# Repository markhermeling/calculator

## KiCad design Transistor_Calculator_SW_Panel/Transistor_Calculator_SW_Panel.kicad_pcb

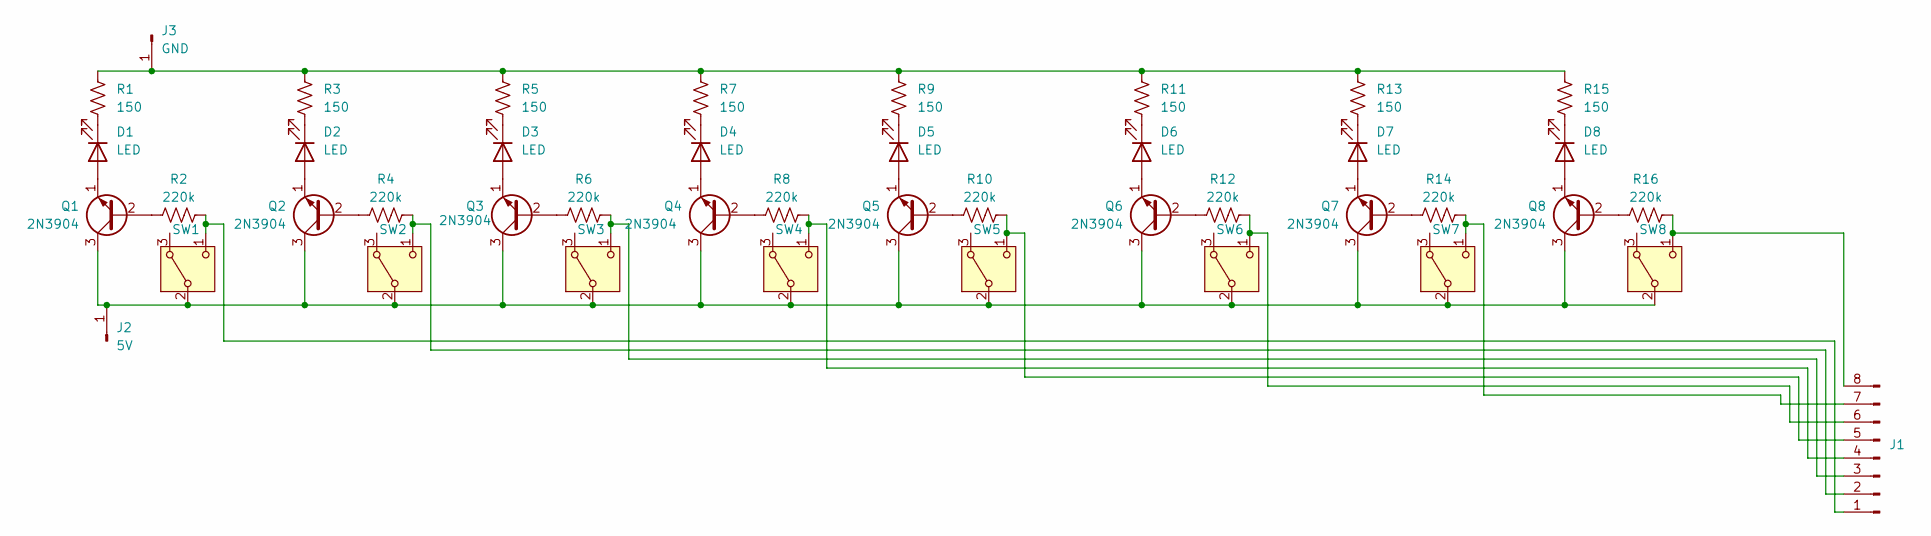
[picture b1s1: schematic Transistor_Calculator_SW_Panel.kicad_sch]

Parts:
D1, D2, D3, D4, D5, D6, D7, D8: LED; LED_D5.0mm_FlatTop
J1: Alex_8-pin
J2: 5V; TestPoint_Pad_D2.0mm
J3: GND; TestPoint_Pad_D2.0mm
Q1, Q2, Q3, Q4, Q5, Q6, Q7, Q8: 2N3904; TO-92L_HandSolder
R1, R3, R5, R7, R9, R11, R13, R15: 150; R_Axial_DIN0204_L3.6mm_D1.6mm_P1.90mm_Vertical
R2, R4, R6, R8, R10, R12, R14, R16: 220k; R_Axial_DIN0204_L3.6mm_D1.6mm_P1.90mm_Vertical
SW1, SW2, SW3, SW4, SW5, SW6, SW7, SW8: Alex_Switch

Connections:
unnamed: D1.2 (A), Q1.1 (E)
unnamed: D1.1 (K), R1.2
unnamed: D2.2 (A), Q2.1 (E)
unnamed: D2.1 (K), R3.2
unnamed: D3.2 (A), Q3.1 (E)
unnamed: D3.1 (K), R5.2
unnamed: D4.2 (A), Q4.1 (E)
unnamed: D4.1 (K), R7.2
unnamed: D5.2 (A), Q5.1 (E)
unnamed: D5.1 (K), R9.2
unnamed: D6.2 (A), Q6.1 (E)
unnamed: D6.1 (K), R11.2
unnamed: D7.2 (A), Q7.1 (E)
unnamed: D7.1 (K), R13.2
unnamed: D8.2 (A), Q8.1 (E)
unnamed: D8.1 (K), R15.2
unnamed: J1.1, R2.2, SW1.1 (C)
unnamed: J1.2, R4.2, SW2.1 (C)
unnamed: J1.3, R6.2, SW3.1 (C)
unnamed: J1.4, R8.2, SW4.1 (C)
unnamed: J1.5, R10.2, SW5.1 (C)
unnamed: J1.6, R12.2, SW6.1 (C)
unnamed: J1.7, R14.2, SW7.1 (C)
unnamed: J1.8, R16.2, SW8.1 (C)
unnamed: J2.1, Q1.3 (C), Q2.3 (C), Q3.3 (C), Q4.3 (C), Q5.3 (C), Q6.3 (C), Q7.3 (C), Q8.3 (C), SW1.2 (B), SW2.2 (B), SW3.2 (B), SW4.2 (B), SW5.2 (B), SW6.2 (B), SW7.2 (B), SW8.2 (B)
unnamed: J3.1, R1.1, R3.1, R5.1, R7.1, R9.1, R11.1, R13.1, R15.1
unnamed: Q1.2 (B), R2.1
unnamed: Q2.2 (B), R4.1
unnamed: Q3.2 (B), R6.1
unnamed: Q4.2 (B), R8.1
unnamed: Q5.2 (B), R10.1
unnamed: Q6.2 (B), R12.1
unnamed: Q7.2 (B), R14.1
unnamed: Q8.2 (B), R16.1

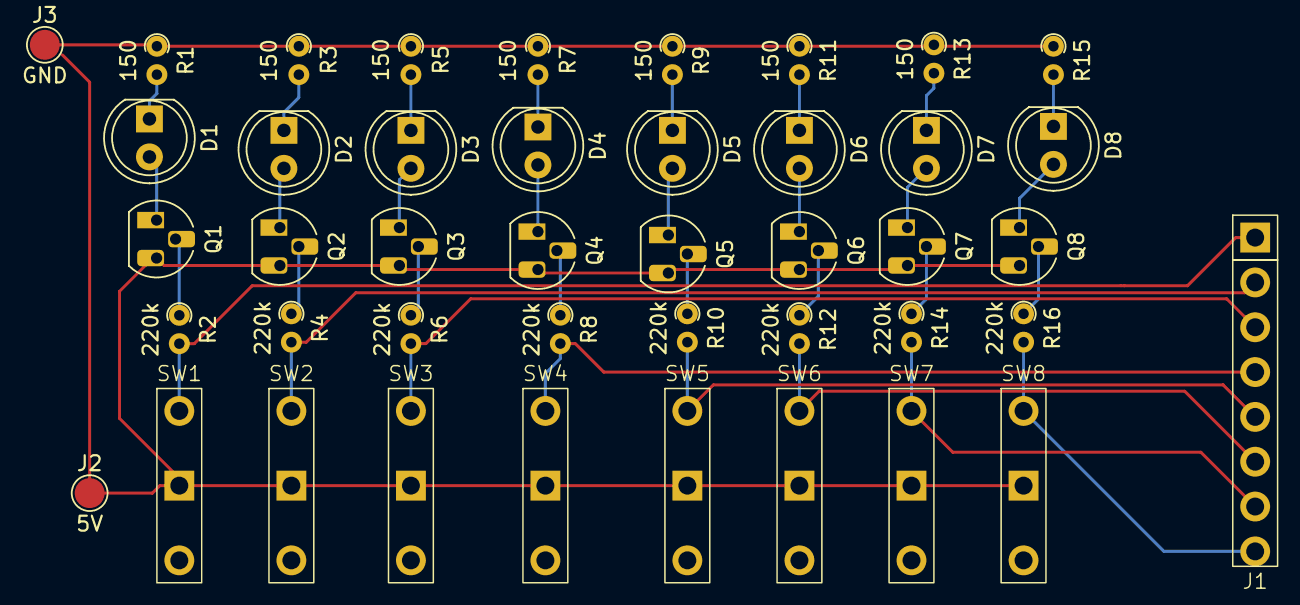
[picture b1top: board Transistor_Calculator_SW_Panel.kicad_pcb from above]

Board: 2 copper layers, 43 parts (0 on the bottom side), 34 nets.

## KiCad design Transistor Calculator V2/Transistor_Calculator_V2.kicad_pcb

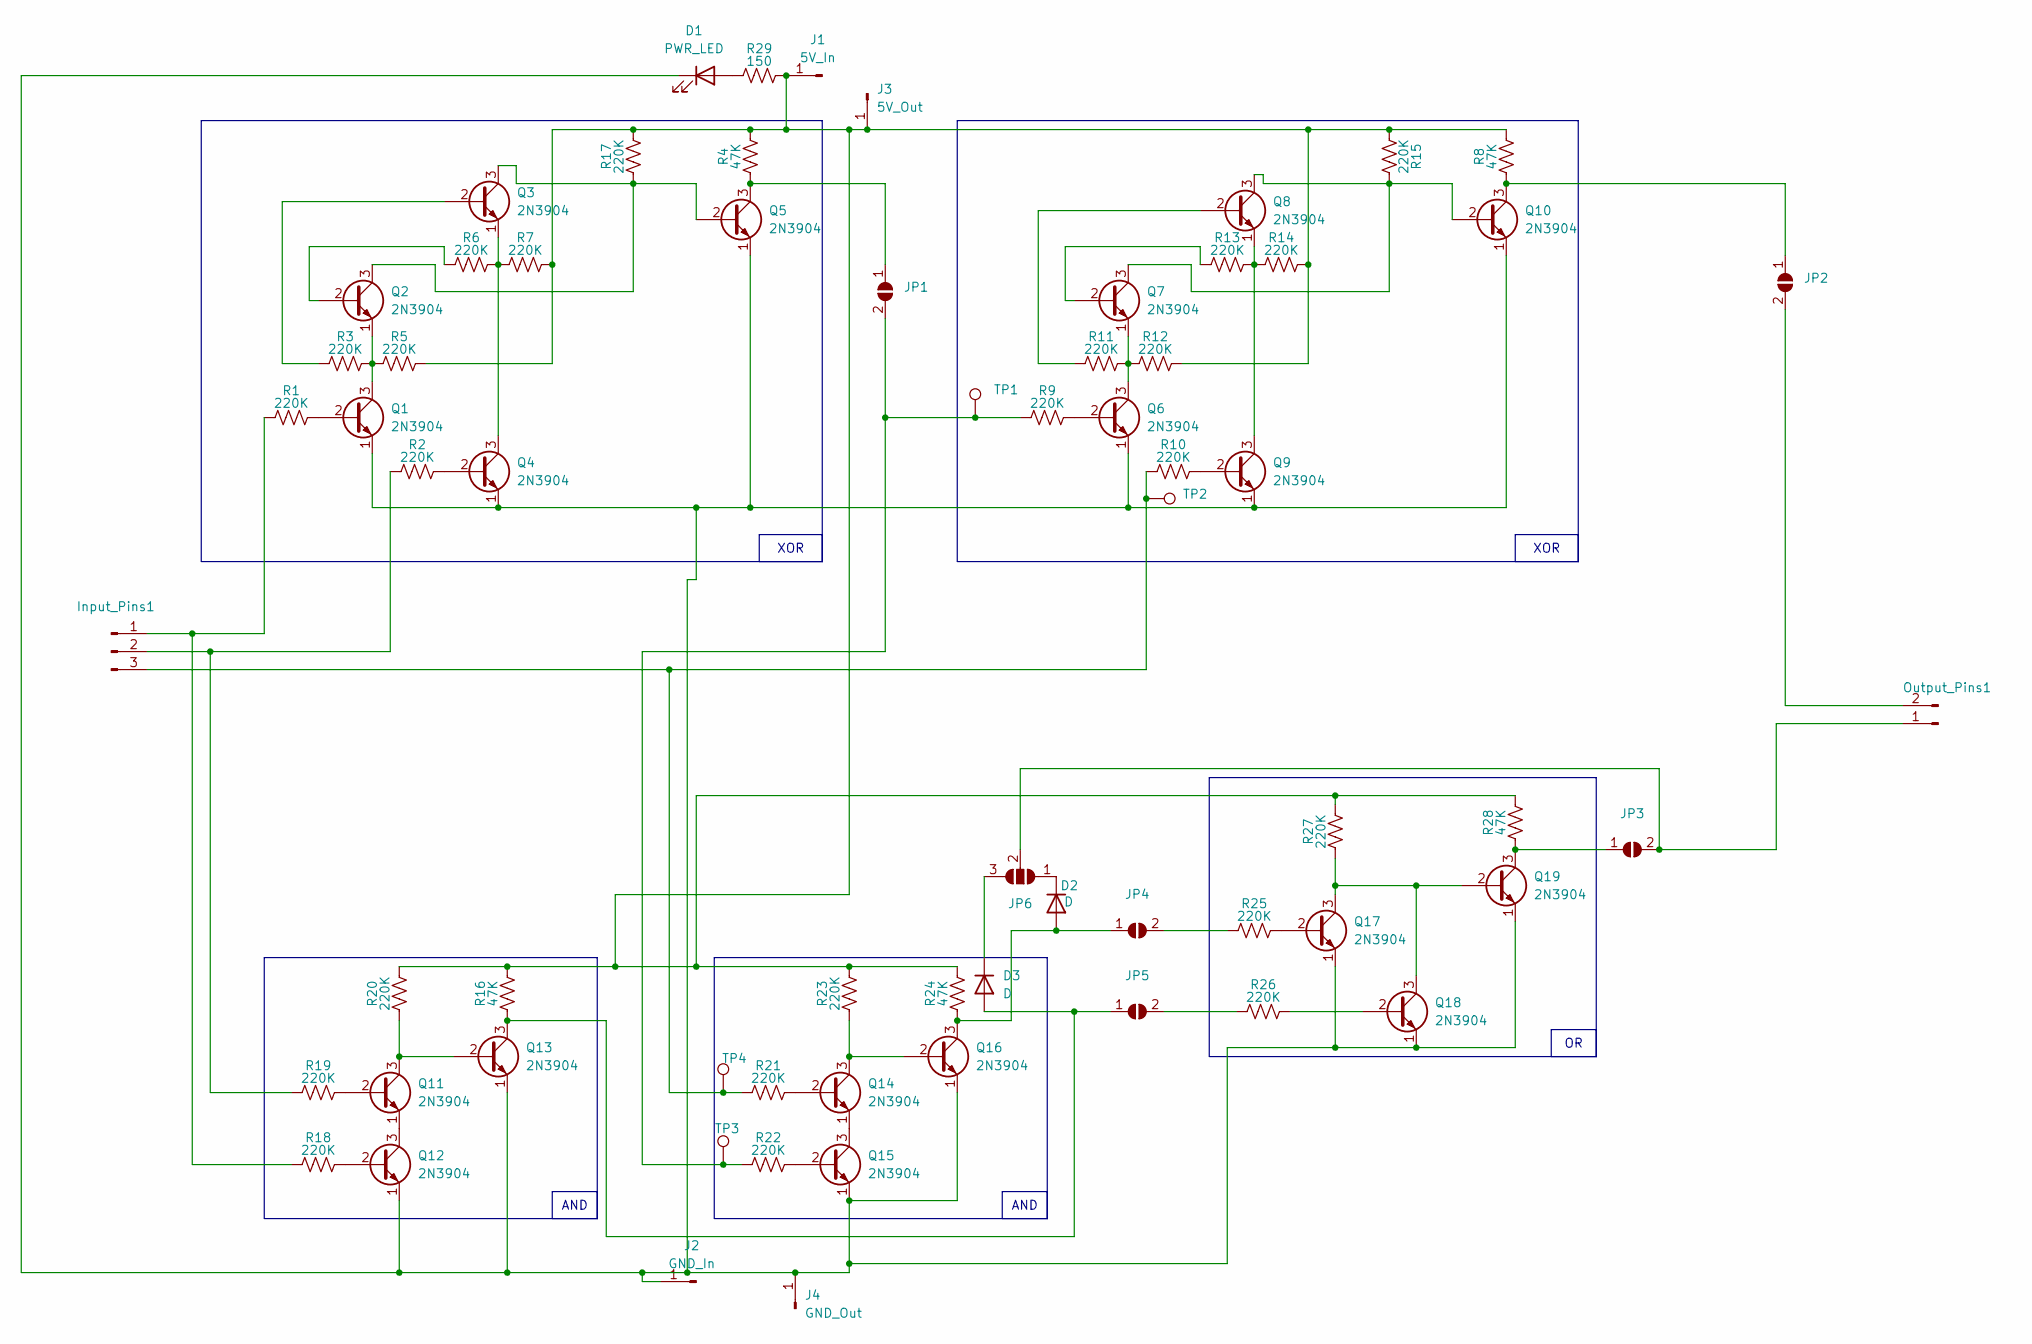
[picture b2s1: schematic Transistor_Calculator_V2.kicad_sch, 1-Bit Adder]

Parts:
D1: PWR_LED; LED_D5.0mm
D2, D3: D; D_A-405_P2.54mm_Vertical_AnodeUp
Input_Pins1: SolderWire-0.5sqmm_1x03_P4.6mm_D0.9mm_OD2.1mm
J1: 5V_In; Pin_D1.0mm_L10.0mm_LooseFit
J2: GND_In; Pin_D1.0mm_L10.0mm_LooseFit
J3: 5V_Out; Pin_D1.0mm_L10.0mm_LooseFit
J4: GND_Out; Pin_D1.0mm_L10.0mm_LooseFit
JP1, JP2, JP3, JP4, JP5: SolderJumper-2_P1.3mm_Open_RoundedPad1.0x1.5mm
JP6: SolderJumper-3_P1.3mm_Open_RoundedPad1.0x1.5mm
Output_Pins1: SolderWire-0.5sqmm_1x02_P4.6mm_D0.9mm_OD2.1mm
Q1, Q2, Q3, Q4, Q5, Q6, Q7, Q8, Q9, Q10, Q11, Q12, Q13, Q14, Q15, Q16, Q17, Q18, Q19: 2N3904; TO-92_HandSolder
R1, R2, R3, R5, R6, R7, R9, R10, R11, R12, R13, R14, R15, R17, R18, R19, R20, R21, R22, R23, R25, R26, R27: 220K; R_Axial_DIN0207_L6.3mm_D2.5mm_P2.54mm_Vertical
R4, R8, R16, R24, R28: 47K; R_Axial_DIN0207_L6.3mm_D2.5mm_P2.54mm_Vertical
R29: 150; R_Axial_DIN0207_L6.3mm_D2.5mm_P2.54mm_Vertical
TP1, TP2, TP3, TP4: TestPoint_Pad_1.0x1.0mm

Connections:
unnamed: D1.2 (A), R29.1
unnamed: D1.1 (K), J2.1, J4.1, Q1.1 (E), Q4.1 (E), Q5.1 (E), Q6.1 (E), Q9.1 (E), Q10.1 (E), Q12.1 (E), Q13.1 (E), Q15.1 (E), Q16.1 (E), Q17.1 (E), Q18.1 (E), Q19.1 (E)
unnamed: D2.2 (A), JP4.1 (A), Q16.3 (C), R24.1
unnamed: D2.1 (K), JP6.1 (A)
unnamed: D3.2 (A), JP5.1 (A), Q13.3 (C), R16.1
unnamed: D3.1 (K), JP6.3 (B)
unnamed: Input_Pins1.1, R1.1, R18.1
unnamed: Input_Pins1.2, R2.1, R19.1
unnamed: Input_Pins1.3, R10.1, R21.1, TP2.1, TP4.1
unnamed: J1.1, J3.1, R4.2, R5.2, R7.2, R8.2, R12.2, R14.2, R15.1, R16.2, R17.2, R20.2, R23.2, R24.2, R27.2, R28.2, R29.2
unnamed: JP1.1 (A), Q5.3 (C), R4.1
unnamed: JP1.2 (B), R9.1, R22.1, TP1.1, TP3.1
unnamed: JP2.1 (A), Q10.3 (C), R8.1
unnamed: JP2.2 (B), Output_Pins1.2
unnamed: JP3.1 (A), Q19.3 (C), R28.1
unnamed: JP3.2 (B), JP6.2 (C), Output_Pins1.1
unnamed: JP4.2 (B), R25.1
unnamed: JP5.2 (B), R26.1
unnamed: Q1.2 (B), R1.2
unnamed: Q1.3 (C), Q2.1 (E), R3.2, R5.1
unnamed: Q2.2 (B), R6.1
unnamed: Q2.3 (C), Q3.3 (C), Q5.2 (B), R17.1
unnamed: Q3.2 (B), R3.1
unnamed: Q3.1 (E), Q4.3 (C), R6.2, R7.1
unnamed: Q4.2 (B), R2.2
unnamed: Q6.2 (B), R9.2
unnamed: Q6.3 (C), Q7.1 (E), R11.2, R12.1
unnamed: Q7.2 (B), R13.1
unnamed: Q8.2 (B), R11.1
unnamed: Q8.1 (E), Q9.3 (C), R13.2, R14.1
unnamed: Q9.2 (B), R10.2
unnamed: Q7.3 (C), Q8.3 (C), Q10.2 (B), R15.2
unnamed: Q11.2 (B), R19.2
unnamed: Q11.3 (C), Q13.2 (B), R20.1
unnamed: Q11.1 (E), Q12.3 (C)
unnamed: Q12.2 (B), R18.2
unnamed: Q14.2 (B), R21.2
unnamed: Q14.3 (C), Q16.2 (B), R23.1
unnamed: Q14.1 (E), Q15.3 (C)
unnamed: Q15.2 (B), R22.2
unnamed: Q17.2 (B), R25.2
unnamed: Q17.3 (C), Q18.3 (C), Q19.2 (B), R27.1
unnamed: Q18.2 (B), R26.2

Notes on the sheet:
XOR
AND

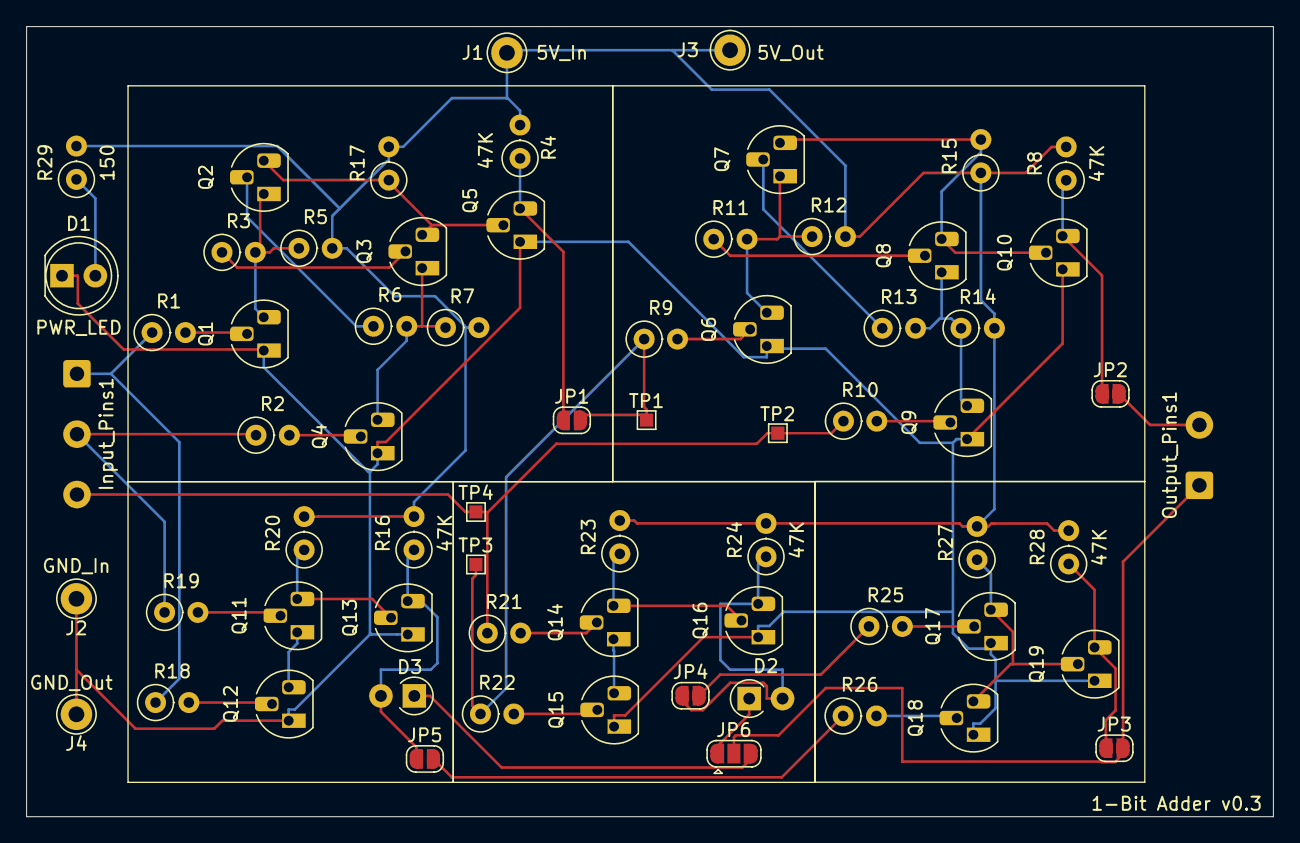
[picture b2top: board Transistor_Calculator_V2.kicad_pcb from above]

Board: 2 copper layers, 95.0 x 60.2 mm, 67 parts (0 on the bottom side), 43 nets.

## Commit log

2024-05-12 This one simulates
2024-05-12 Devcontainer
2024-05-12 added output labels
2024-05-12 Switch to newer version
2024-05-12 Fix mapping of .ssh keys
2024-05-12 Changed control of the input
2024-05-12 Start of auto test scripts
2024-05-12 Change voltage connectors
2024-05-12 script to run through the truth table
2024-05-12 run.sh runs through the options and prints the truth table
2024-05-12 fix inconsistency in file due to merge conflict
2024-05-12 dont need results.outp
2024-05-12 Removed the part that was breaking it.
2024-05-13 Initial file commit
2024-05-13 Removed the other files
2024-05-14 scripting
2024-05-14 PR to main
2024-05-14 Kicad container
2024-05-14 debug
2024-05-14 trigger
2024-05-14 new container
2024-05-14 hardcode
2024-05-14 source
2024-05-14 duh, checkout
2024-05-14 v4 of the action
2024-05-14 Latest files from Alex
2024-05-14 remove test ports
2024-05-14 fix q5
2024-05-15 Changes some routing. Added LED for debugging.
2024-05-15 update transistors
2024-05-15 add carry test
2024-05-15 renamed vinc
2024-05-15 Include vinc into the truth table
2024-05-15 Add files via upload
    This is the schematic that works for me
2024-05-16 Small changes
2024-05-18 removed LED
2024-05-18 Added diode and changes some of the pcb placements
2024-05-18 Fixed the carry bit problem for the schematic
2024-05-18 Added diode to replace OR gate
2024-05-19 Switch panel + small changes
2024-05-26 Small changes and attempt to make a simulation model for the SW
2024-05-26 Other small changes
2026-03-28 Add Java app to calculate sleeps until next DST change
    Takes an optional date (YYYY-MM-DD) and optional timezone as command-line
    arguments and prints how many sleeps remain until the next summer/winter
    time change, using Java's ZoneRules for accurate DST transition data.
    https://claude.ai/code/session_01PF8BWTD7y8USt7NshQe8AW
2026-03-28 Add .gitignore to exclude Java compiled class files
    https://claude.ai/code/session_01PF8BWTD7y8USt7NshQe8AW
2026-04-18 Add Zephyr firmware for Pico W garage door controller
    MicroPython replaced with a Zephyr RTOS application targeting
    rpi_pico/rp2040/w. The firmware connects to WiFi, speaks MQTT,
    publishes Home Assistant MQTT discovery so the door appears as a
    cover entity automatically, and pulses a GPIO-driven relay/transistor
    to simulate the wall-button press. An optional reed-switch input on
    GP14 reports open/closed state back over MQTT.
